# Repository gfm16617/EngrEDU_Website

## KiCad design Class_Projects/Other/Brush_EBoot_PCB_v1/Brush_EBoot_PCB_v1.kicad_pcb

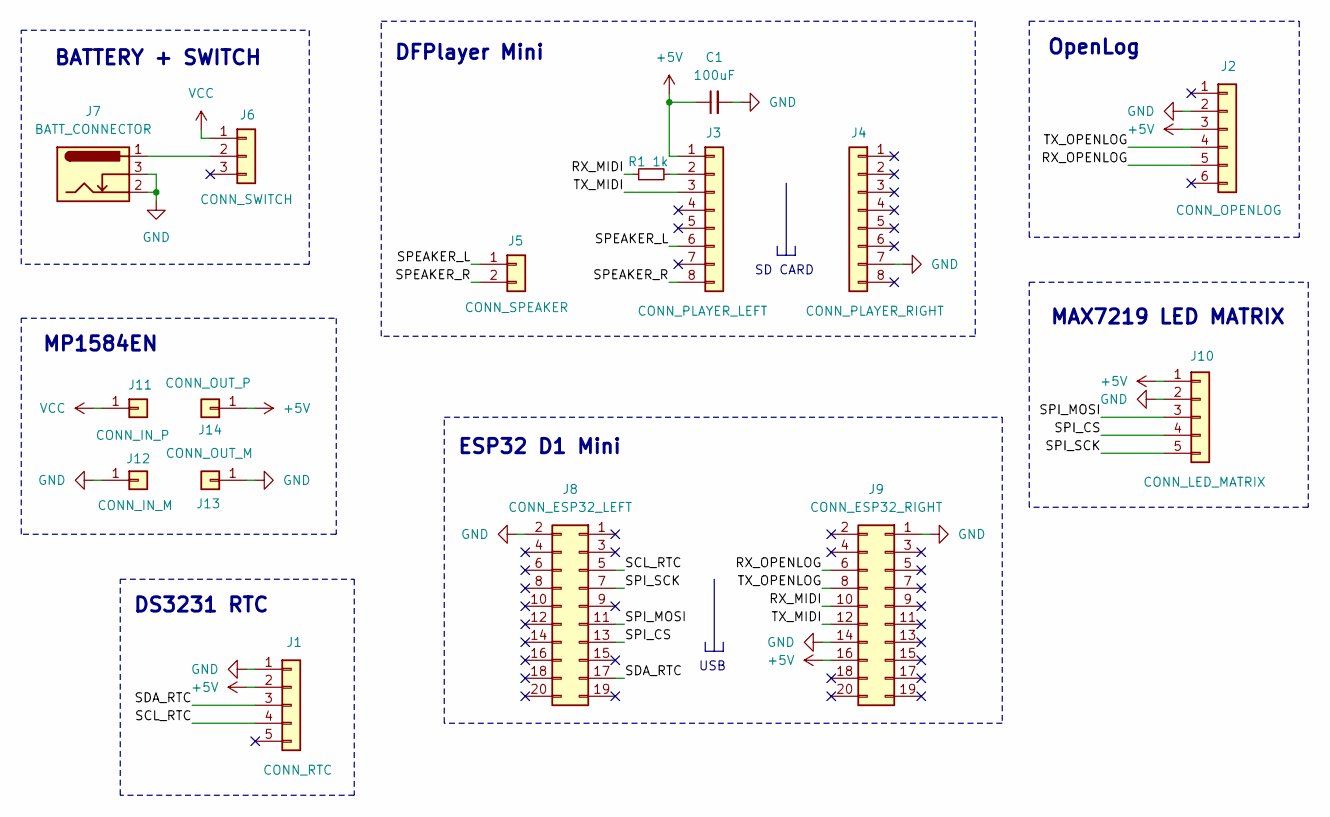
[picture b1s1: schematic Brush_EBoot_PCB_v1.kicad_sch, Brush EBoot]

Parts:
C1: 100uF; CP_Radial_D8.0mm_P3.50mm
J1: CONN_RTC; PinSocket_1x05_P2.54mm_Vertical
J2: CONN_OPENLOG; PinSocket_1x06_P2.54mm_Vertical
J3: CONN_PLAYER_LEFT; PinSocket_1x08_P2.54mm_Vertical
J4: CONN_PLAYER_RIGHT; PinSocket_1x08_P2.54mm_Vertical
J5: CONN_SPEAKER; JST_XH_B2B-XH-A_1x02_P2.50mm_Vertical
J6: CONN_SWITCH; JST_XH_B3B-XH-A_1x03_P2.50mm_Vertical
J7: BATT_CONNECTOR; BarrelJack_Horizontal
J8: CONN_ESP32_LEFT; PinSocket_2x10_P2.54mm_Vertical
J9: CONN_ESP32_RIGHT; PinSocket_2x10_P2.54mm_Vertical
J10: CONN_LED_MATRIX; JST_XH_B5B-XH-A_1x05_P2.50mm_Vertical
J11: CONN_IN_P; PinHeader_1x01_P2.54mm_Vertical
J12: CONN_IN_M; PinHeader_1x01_P2.54mm_Vertical
J13: CONN_OUT_M; PinHeader_1x01_P2.54mm_Vertical
J14: CONN_OUT_P; PinHeader_1x01_P2.54mm_Vertical
R1: 1k; R_Axial_DIN0207_L6.3mm_D2.5mm_P10.16mm_Horizontal

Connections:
+5V: C1.1, J1.2, J2.3, J3.1, J9.16, J10.1, J14.1
/RX_MIDI: J9.10, R1.1
/RX_OPENLOG: J2.5, J9.6
/SCL_RTC: J1.4, J8.5
/SDA_RTC: J1.3, J8.17
/SPEAKER_L: J3.6, J5.1
/SPEAKER_R: J3.8, J5.2
/SPI_CS: J8.13, J10.4
/SPI_MOSI: J8.11, J10.3
/SPI_SCK: J8.7, J10.5
/TX_MIDI: J3.3, J9.12
/TX_OPENLOG: J2.4, J9.8
GND: C1.2, J1.1, J2.2, J4.7, J7.2, J7.3, J8.2, J9.1, J9.14, J10.2, J12.1, J13.1
unnamed: J3.2, R1.2
unnamed: J6.2, J7.1
VCC: J6.1, J11.1

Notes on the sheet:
MAX7219 LED MATRIX
OpenLog
ESP32 D1 Mini
USB
MP1584EN
DFPlayer Mini
SD CARD
DS3231 RTC
BATTERY + SWITCH

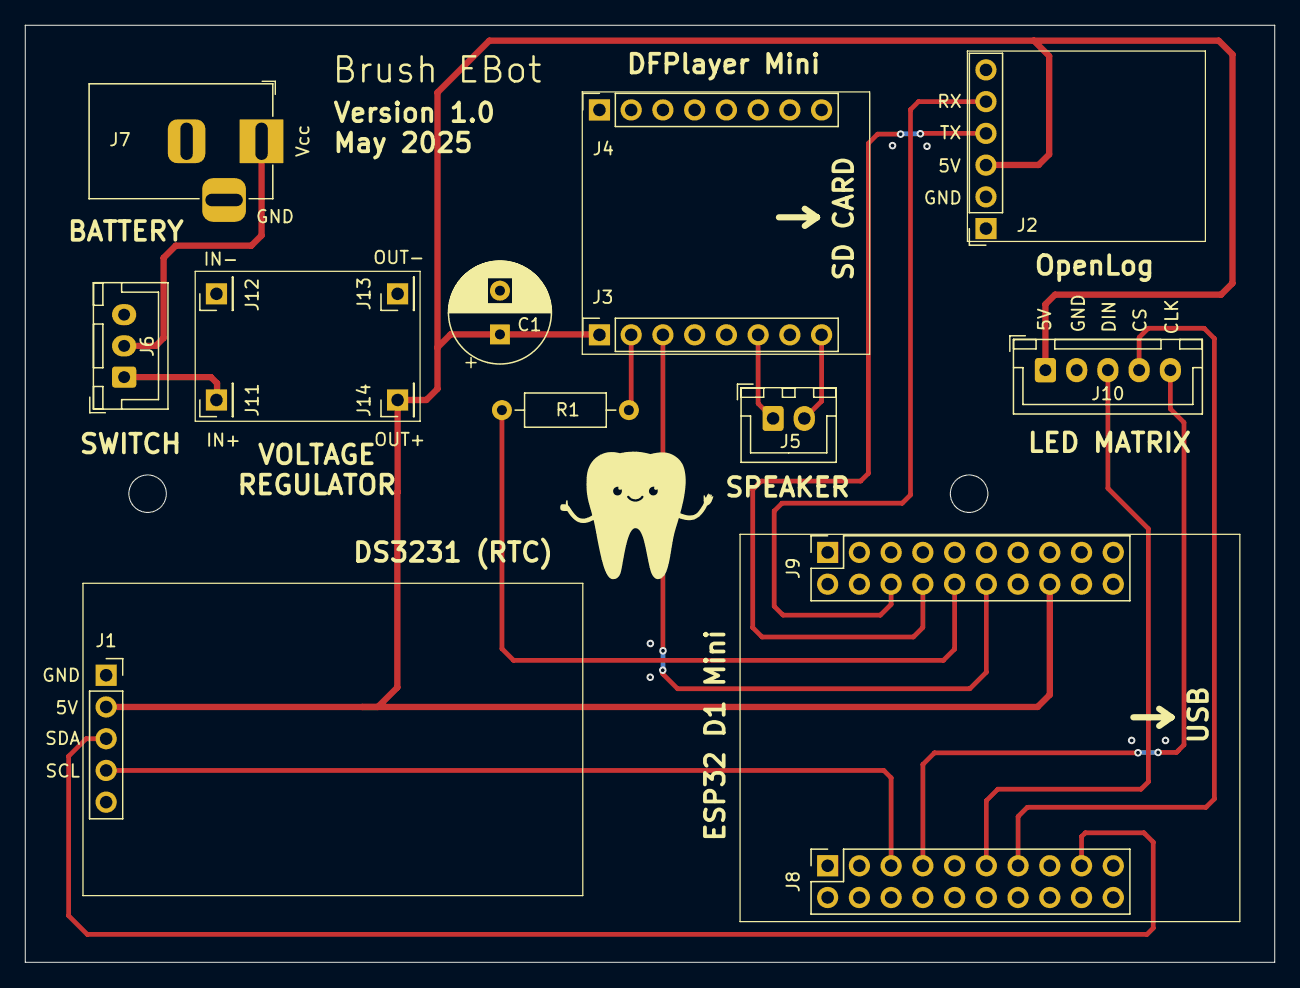
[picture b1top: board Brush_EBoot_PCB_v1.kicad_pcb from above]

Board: 2 copper layers, 100.0 x 75.0 mm, 16 parts (0 on the bottom side), 16 nets.

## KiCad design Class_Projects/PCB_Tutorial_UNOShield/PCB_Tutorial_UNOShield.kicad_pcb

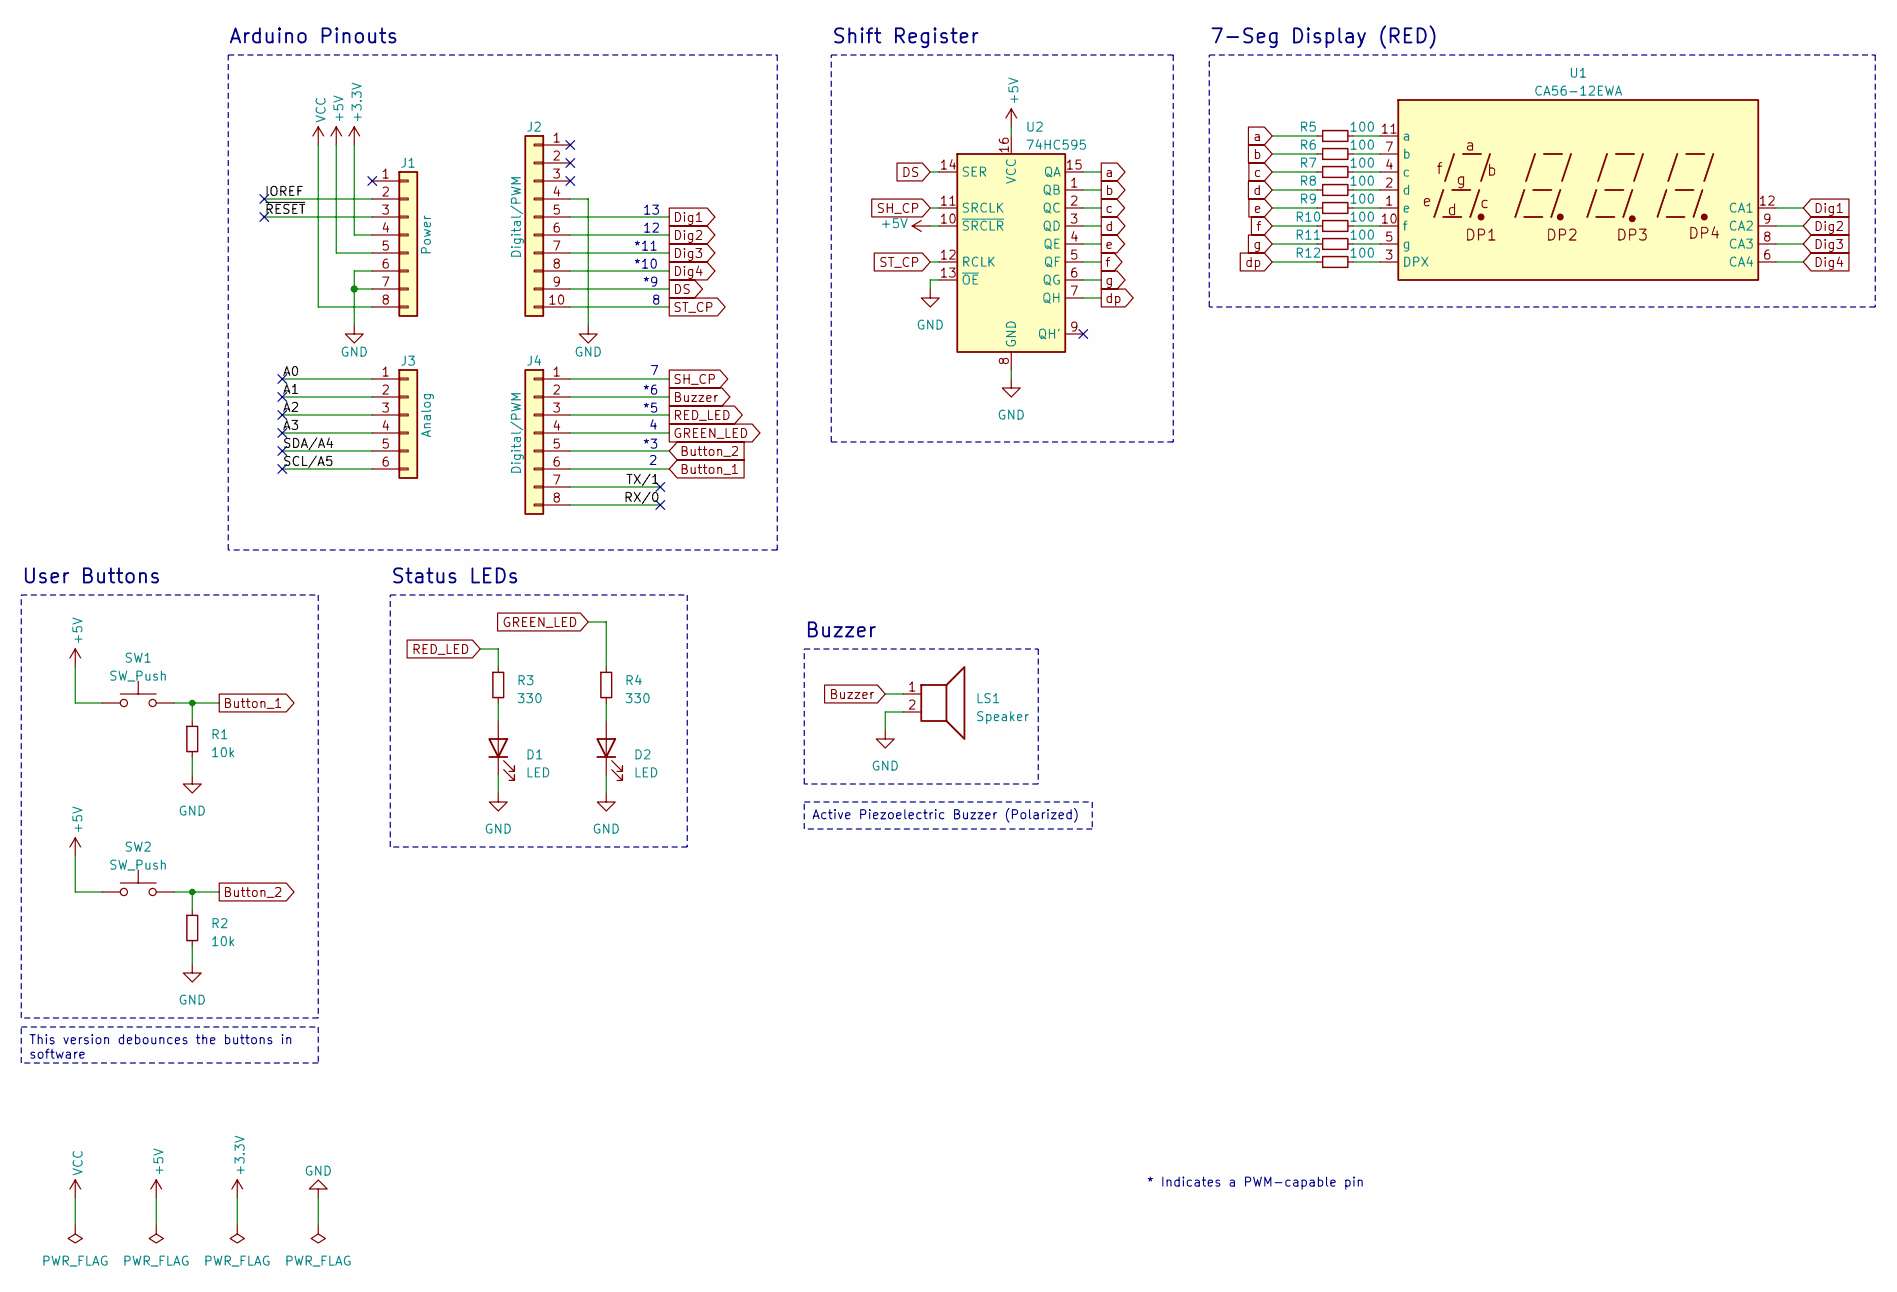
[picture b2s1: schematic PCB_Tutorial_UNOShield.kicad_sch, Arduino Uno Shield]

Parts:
D1, D2: LED; LED_D5.0mm
J1: Power; PinSocket_1x08_P2.54mm_Vertical
J2: Digital/PWM; PinSocket_1x10_P2.54mm_Vertical
J3: Analog; PinSocket_1x06_P2.54mm_Vertical
J4: Digital/PWM; PinSocket_1x08_P2.54mm_Vertical
LS1: Speaker; Buzzer_12x9.5RM7.6
R1, R2: 10k; R_Axial_DIN0207_L6.3mm_D2.5mm_P10.16mm_Horizontal
R3, R4: 330; R_Axial_DIN0207_L6.3mm_D2.5mm_P10.16mm_Horizontal
R5, R6, R7, R8, R9, R10, R11, R12: 100; R_Axial_DIN0207_L6.3mm_D2.5mm_P10.16mm_Horizontal
SW1, SW2: SW_Push; SW_PUSH-12mm
U1: CA56-12EWA
U2: 74HC595; DIP-16_W7.62mm_Socket_LongPads

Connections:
+3V3: J1.4
+5V: J1.5, SW1.1, SW2.1, U2.10 (~SRCLR), U2.16 (VCC)
/A0: J3.1
/A1: J3.2
/A2: J3.3
/A3: J3.4
/IOREF: J1.2
/RX/0: J4.8
/SCL/A5: J3.6
/SDA/A4: J3.5
/TX/1: J4.7
/~RESET: J1.3
Button_1: J4.6, R1.1, SW1.2
Button_2: J4.5, R2.1, SW2.2
Buzzer: J4.2, LS1.1
DS: J2.9, U2.14 (SER)
Dig1: J2.5, U1.12 (CA1)
Dig2: J2.6, U1.9 (CA2)
Dig3: J2.7, U1.8 (CA3)
Dig4: J2.8, U1.6 (CA4)
GND: D1.1 (K), D2.1 (K), J1.6, J1.7, J2.4, LS1.2, R1.2, R2.2, U2.8 (GND), U2.13 (~OE)
GREEN_LED: J4.4, R4.1
unnamed: D1.2 (A), R3.2
unnamed: D2.2 (A), R4.2
unnamed: R12.2, U1.3 (DPX)
unnamed: R5.2, U1.11 (a)
unnamed: R6.2, U1.7 (b)
unnamed: R7.2, U1.4 (c)
unnamed: R8.2, U1.2 (d)
unnamed: R9.2, U1.1 (e)
unnamed: R10.2, U1.10 (f)
unnamed: R11.2, U1.5 (g)
RED_LED: J4.3, R3.1
SH_CP: J4.1, U2.11 (SRCLK)
ST_CP: J2.10, U2.12 (RCLK)
VCC: J1.8
a: R5.1, U2.15 (QA)
b: R6.1, U2.1 (QB)
c: R7.1, U2.2 (QC)
d: R8.1, U2.3 (QD)
dp: R12.1, U2.7 (QH)
e: R9.1, U2.4 (QE)
f: R10.1, U2.5 (QF)
g: R11.1, U2.6 (QG)

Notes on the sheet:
Active Piezoelectric Buzzer (Polarized)
This version debounces the buttons in software
Shift Register
*10
Status LEDs
Arduino Pinouts
User Buttons
Buzzer
* Indicates a PWM-capable pin
7-Seg Display (RED)
*11

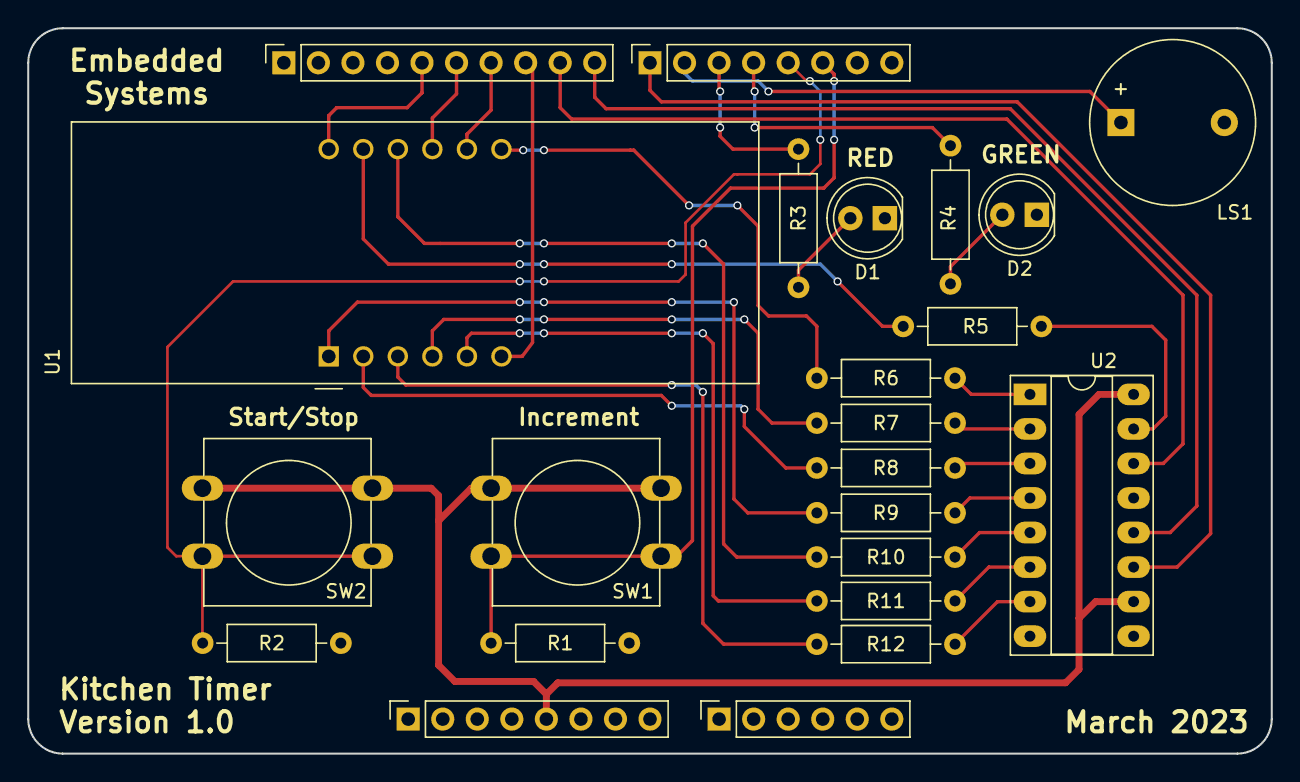
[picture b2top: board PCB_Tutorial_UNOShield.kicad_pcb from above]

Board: 2 copper layers, 91.4 x 53.3 mm, 23 parts (0 on the bottom side), 32 nets.

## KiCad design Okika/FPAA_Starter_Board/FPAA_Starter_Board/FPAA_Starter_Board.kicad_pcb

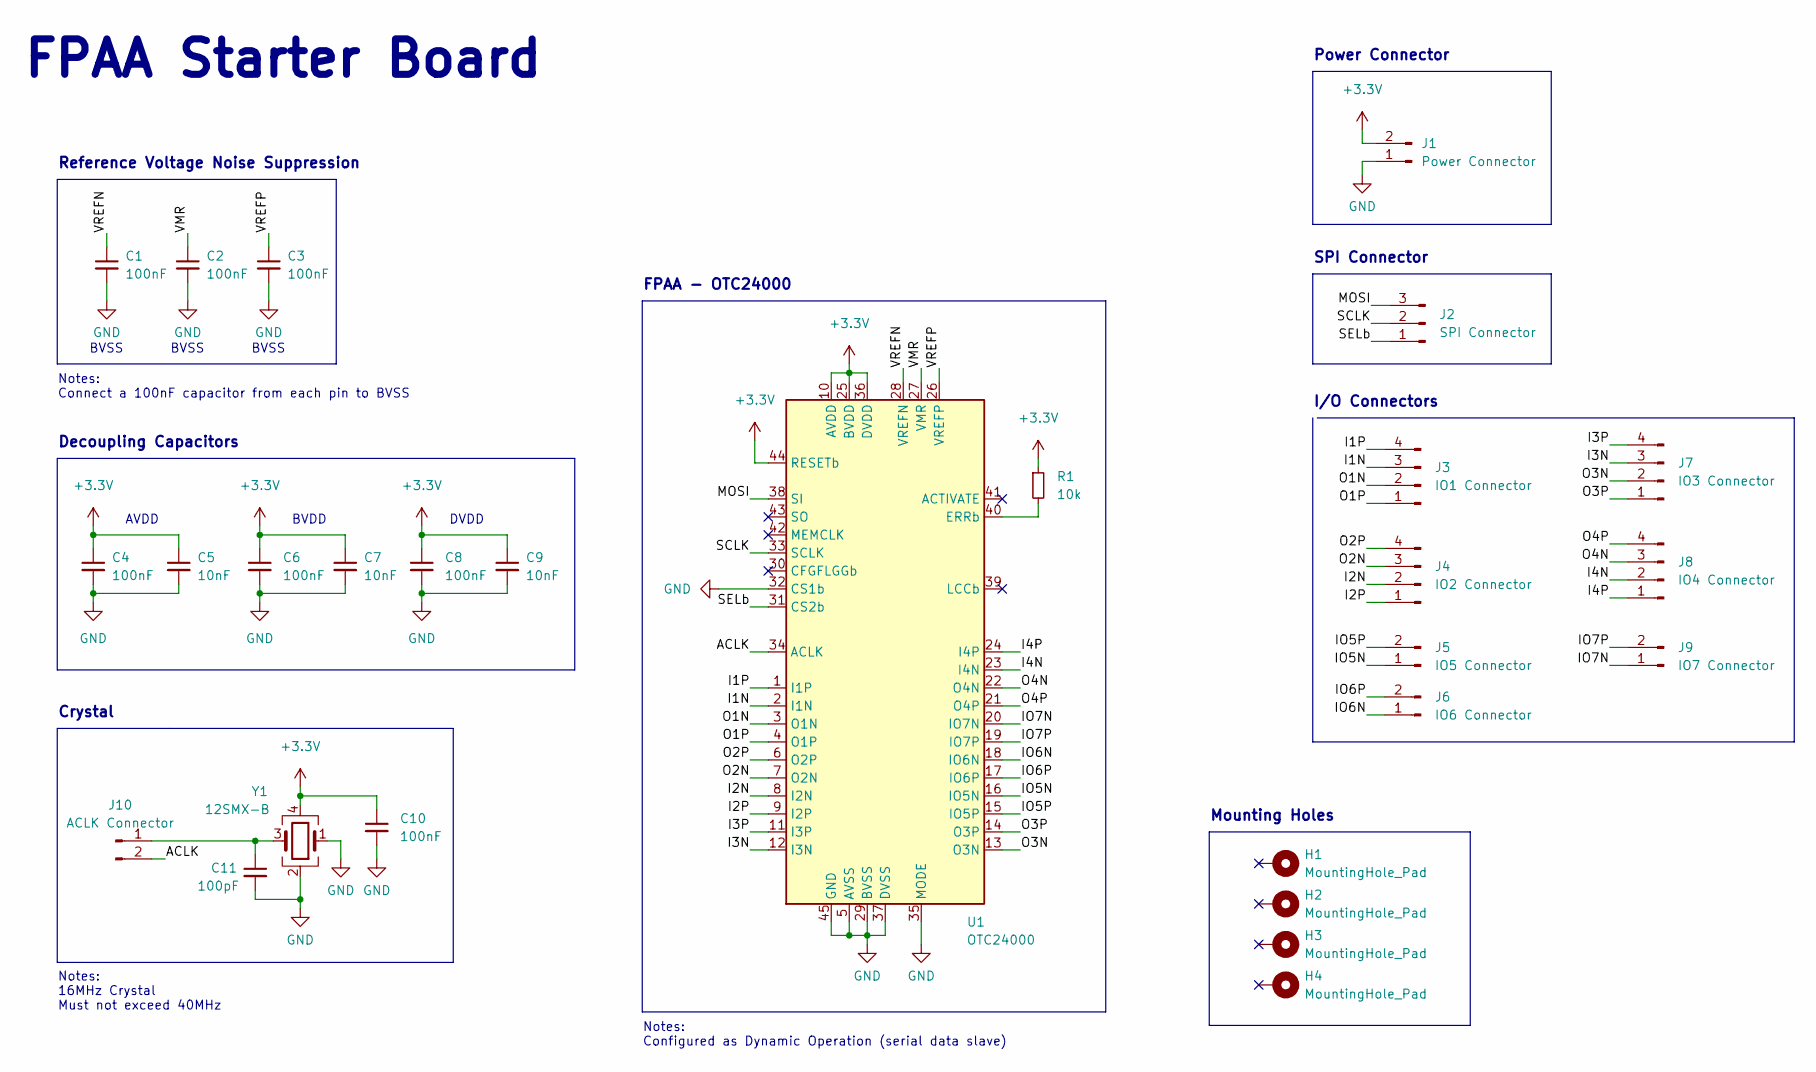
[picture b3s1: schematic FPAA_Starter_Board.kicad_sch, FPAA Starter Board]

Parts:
C1, C2, C3, C4, C6, C8, C10: 100nF; C_0603_1608Metric; Part # 0603YC104J4T4A
C5, C7, C9: 10nF; C_0603_1608Metric; Part # 06033C103JAT4A
C11: 100pF; C_0603_1608Metric; Part # VJ0603A101GXQCW1BC
H1, H2, H3, H4: MountingHole_Pad; MountingHole_3.2mm_M3_Pad_Via
J1: Power Connector; PinHeader_1x02_P2.54mm_Vertical
J2: SPI Connector; PinHeader_1x03_P2.54mm_Vertical
J3: IO1 Connector; PinHeader_1x04_P2.54mm_Vertical
J4: IO2 Connector; PinHeader_1x04_P2.54mm_Vertical
J5: IO5 Connector; PinHeader_1x02_P2.54mm_Vertical
J6: IO6 Connector; PinHeader_1x02_P2.54mm_Vertical
J7: IO3 Connector; PinHeader_1x04_P2.54mm_Vertical
J8: IO4 Connector; PinHeader_1x04_P2.54mm_Vertical
J9: IO7 Connector; PinHeader_1x02_P2.54mm_Vertical
J10: ACLK Connector; PinHeader_1x02_P2.54mm_Vertical
R1: 10k; R_0603_1608Metric; Part # RT0603FRD0710KL
U1: OTC24000; QFN-44-1EP_7x7mm_P0.5mm_EP5.15x5.15mm; Part # OTC24000
Y1: 12SMX-B; Crystal_SMD_7050-4Pin_7.0x5.0mm; Part # LFXTAL026392Reel

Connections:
+3V3: C4.1, C5.1, C6.1, C7.1, C8.1, C9.1, C10.1, J1.2, R1.1, U1.10 (AVDD), U1.25 (BVDD), U1.36 (DVDD), U1.44 (RESETb), Y1.4
/ACLK: J10.2, U1.34 (ACLK)
/I1N: J3.3, U1.2 (I1N)
/I1P: J3.4, U1.1 (I1P)
/I2N: J4.2, U1.8 (I2N)
/I2P: J4.1, U1.9 (I2P)
/I3N: J7.3, U1.12 (I3N)
/I3P: J7.4, U1.11 (I3P)
/I4N: J8.2, U1.23 (I4N)
/I4P: J8.1, U1.24 (I4P)
/IO5N: J5.1, U1.16 (IO5N)
/IO5P: J5.2, U1.15 (IO5P)
/IO6N: J6.1, U1.18 (IO6N)
/IO6P: J6.2, U1.17 (IO6P)
/IO7N: J9.1, U1.20 (IO7N)
/IO7P: J9.2, U1.19 (IO7P)
/MOSI: J2.3, U1.38 (SI)
/O1N: J3.2, U1.3 (O1N)
/O1P: J3.1, U1.4 (O1P)
/O2N: J4.3, U1.7 (O2N)
/O2P: J4.4, U1.6 (O2P)
/O3N: J7.2, U1.13 (O3N)
/O3P: J7.1, U1.14 (O3P)
/O4N: J8.3, U1.22 (O4N)
/O4P: J8.4, U1.21 (O4P)
/SCLK: J2.2, U1.33 (SCLK)
/SELb: J2.1, U1.31 (CS2b)
/VMR: C2.1, U1.27 (VMR)
/VREFN: C1.1, U1.28 (VREFN)
/VREFP: C3.1, U1.26 (VREFP)
GND: C1.2, C2.2, C3.2, C4.2, C5.2, C6.2, C7.2, C8.2, C9.2, C10.2, C11.2, J1.1, U1.5 (AVSS), U1.29 (BVSS), U1.32 (CS1b), U1.35 (MODE), U1.37 (DVSS), U1.45 (GND), Y1.1, Y1.2
unnamed: C11.1, J10.1, Y1.3
unnamed: R1.2, U1.40 (ERRb)

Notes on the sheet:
BVSS
DVDD
BVDD
Notes: 16MHz Crystal Must not exceed 40MHz
Decoupling Capacitors
Reference Voltage Noise Suppression
Power Connector
FPAA - OTC24000
Mounting Holes
Notes: Connect a 100nF capacitor from each pin to BVSS
AVDD
FPAA Starter Board
Crystal
SPI Connector
Notes: Configured as Dynamic Operation (serial data slave)
I/O Connectors

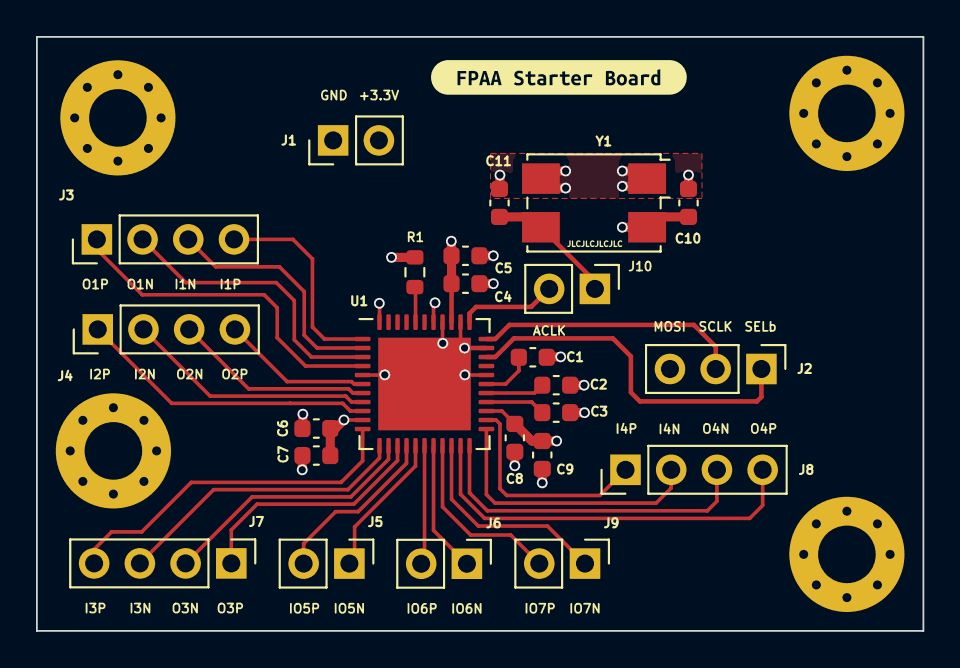
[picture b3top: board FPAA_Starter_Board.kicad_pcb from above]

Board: 4 copper layers, 49.2 x 33.0 mm, 29 parts (0 on the bottom side), 33 nets.

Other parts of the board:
kibuzzard-623065F3: G***; kibuzzard-623065F3

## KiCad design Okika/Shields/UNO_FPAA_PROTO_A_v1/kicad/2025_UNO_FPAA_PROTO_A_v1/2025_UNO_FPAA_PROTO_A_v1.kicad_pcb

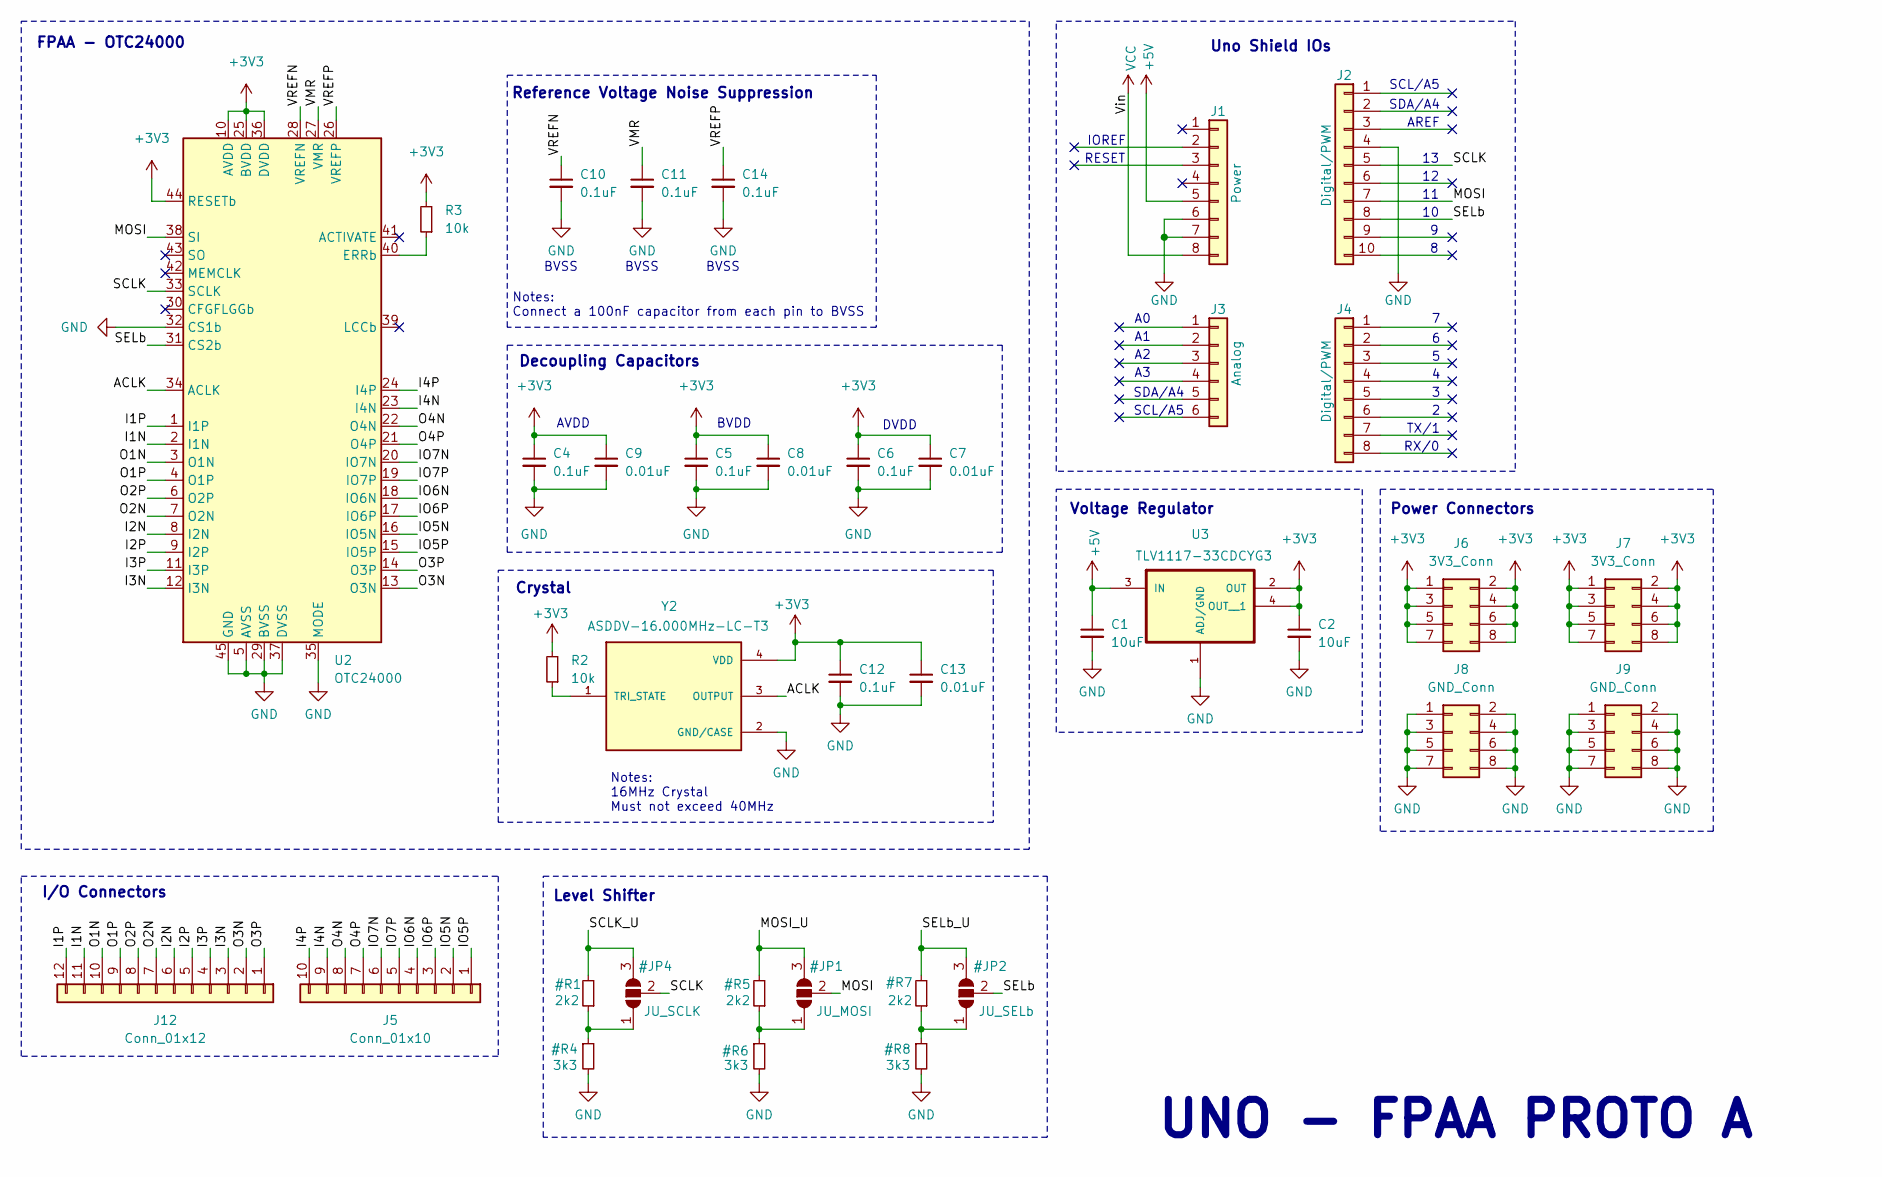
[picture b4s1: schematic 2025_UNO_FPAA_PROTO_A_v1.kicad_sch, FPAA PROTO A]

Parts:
C1, C2: 10uF; C_0805_2012Metric; Part # EMK212BB7106KG-T
C4, C5, C6, C10, C11, C12, C14: 0.1uF; C_0805_2012Metric; Part # KAM21BR71H104JT
C7, C8, C9, C13: 0.01uF; C_0805_2012Metric; Part # KAM21BR72A103KM
J1: Power; PinSocket_1x08_P2.54mm_Vertical
J2: Digital/PWM; PinSocket_1x10_P2.54mm_Vertical
J3: Analog; PinSocket_1x06_P2.54mm_Vertical
J4: Digital/PWM; PinSocket_1x08_P2.54mm_Vertical
J5: Conn_01x10; PinHeader_1x10_P2.54mm_Vertical
J6, J7: 3V3_Conn; PinHeader_2x04_P2.54mm_Vertical
J8, J9: GND_Conn; PinHeader_2x04_P2.54mm_Vertical
J12: Conn_01x12; PinHeader_1x12_P2.54mm_Vertical
R2, R3: 10k; R_0805_2012Metric; Part # RNCE0805BTE10K0
U2: OTC24000; QFN-44-1EP_7x7mm_P0.5mm_EP5.15x5.15mm; Part # OTC24000
U3: TLV1117-33CDCYG3; SOT230P700X180-4N; Part # TLV1117-33CDCY
Y2: ASDDV-16.000MHz-LC-T3; XTAL_ASDDV-16.000MHz-LC-T3; PARTREV 09.09.2019

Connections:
+3V3: C2.1, C4.1, C5.1, C6.1, C7.1, C8.1, C9.1, C12.1, C13.1, J6.1, J6.2, J6.3, J6.4, J6.5, J6.6, J6.7, J6.8, J7.1, J7.2, J7.3, J7.4, J7.5, J7.6, J7.7, J7.8, R2.2, R3.2, U2.10 (AVDD), U2.25 (BVDD), U2.36 (DVDD), U2.44 (RESETb), U3.2 (OUT), U3.4 (OUT__1), Y2.4 (VDD)
+5V: C1.1, J1.5, U3.3 (IN)
/ACLK: U2.34 (ACLK), Y2.3 (OUTPUT)
/I1N: J12.11, U2.2 (I1N)
/I1P: J12.12, U2.1 (I1P)
/I2N: J12.6, U2.8 (I2N)
/I2P: J12.5, U2.9 (I2P)
/I3N: J12.3, U2.12 (I3N)
/I3P: J12.4, U2.11 (I3P)
/I4N: J5.9, U2.23 (I4N)
/I4P: J5.10, U2.24 (I4P)
/IO5N: J5.2, U2.16 (IO5N)
/IO5P: J5.1, U2.15 (IO5P)
/IO6N: J5.4, U2.18 (IO6N)
/IO6P: J5.3, U2.17 (IO6P)
/IO7N: J5.6, U2.20 (IO7N)
/IO7P: J5.5, U2.19 (IO7P)
/O1N: J12.10, U2.3 (O1N)
/O1P: J12.9, U2.4 (O1P)
/O2N: J12.7, U2.7 (O2N)
/O2P: J12.8, U2.6 (O2P)
/O3N: J12.2, U2.13 (O3N)
/O3P: J12.1, U2.14 (O3P)
/O4N: J5.8, U2.22 (O4N)
/O4P: J5.7, U2.21 (O4P)
/VMR: C11.1, U2.27 (VMR)
/VREFN: C10.1, U2.28 (VREFN)
/VREFP: C14.1, U2.26 (VREFP)
unnamed: R3.1, U2.40 (ERRb)
unnamed: R2.1, Y2.1 (TRI_STATE)
VCC: J1.8

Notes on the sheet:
BVSS
RESET
Notes: Connect a 100nF capacitor from each pin to BVSS
Uno Shield IOs
DVDD
UNO - FPAA PROTO A
AVDD
Notes: 16MHz Crystal Must not exceed 40MHz
IOREF
Power Connectors
AREF
Level Shifter
SDA/A4
SCL/A5
BVDD
Crystal
RX/0
I/O Connectors
Decoupling Capacitors
Voltage Regulator
Reference Voltage Noise Suppression
TX/1
FPAA - OTC24000

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
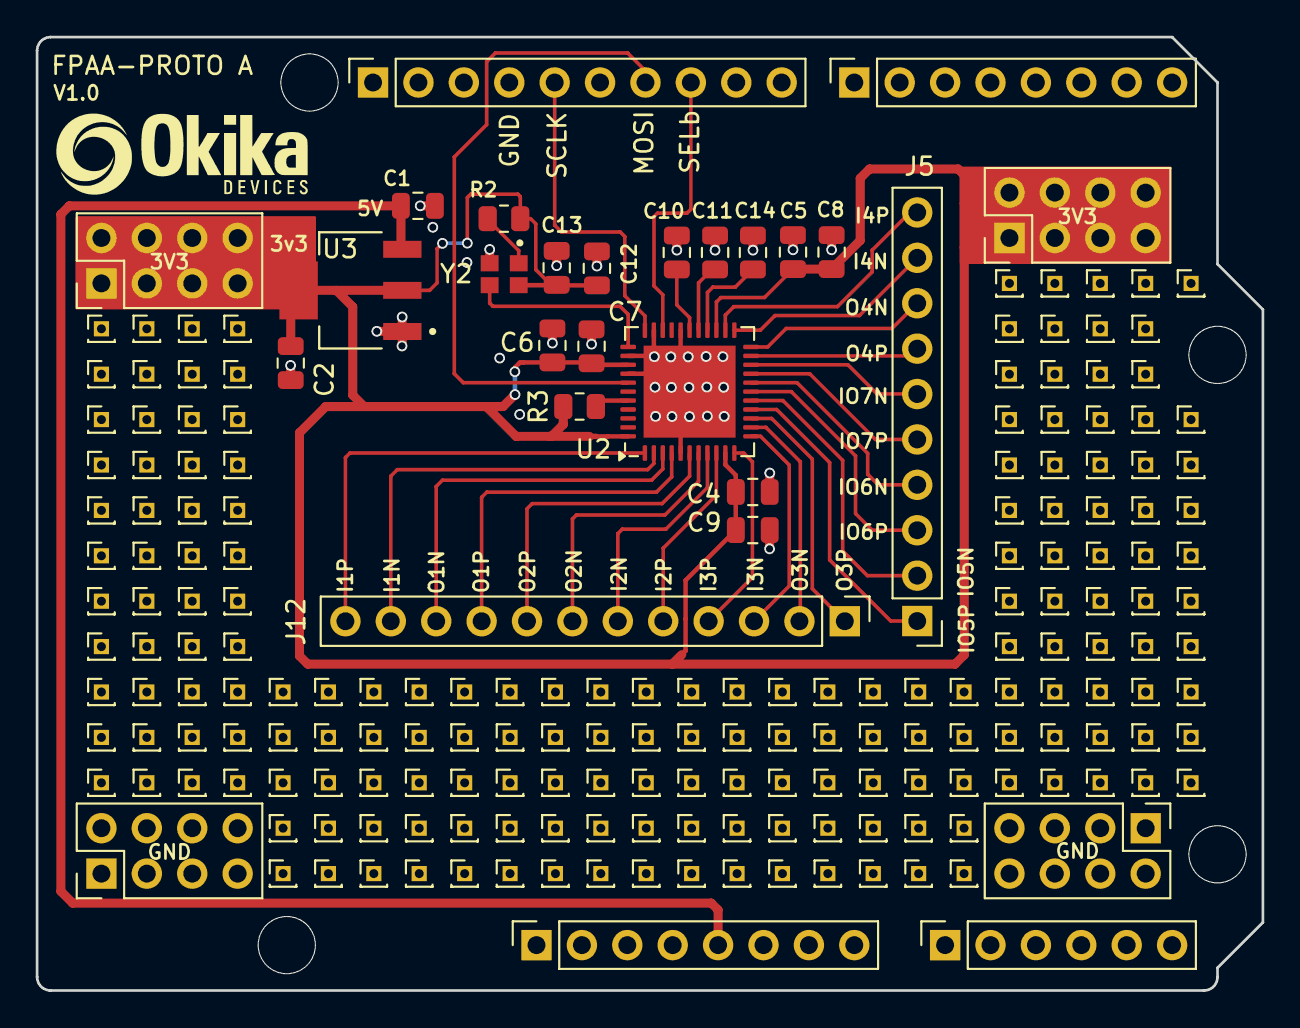
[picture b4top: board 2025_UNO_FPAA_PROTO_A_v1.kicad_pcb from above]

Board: 2 copper layers, 68.6 x 53.3 mm, 32 parts (0 on the bottom side), 34 nets.

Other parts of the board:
MH1, MH2, MH3, MH4: MountingHole_3.2mm
